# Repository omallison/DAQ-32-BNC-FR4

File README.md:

# Quartz Breakout (DAQ-32-BNC-FR4 Version)

Made in KiCad 9.0.7

- PCB is the panel (thickness: 3.2mm)
- Local (meant for short ribbon cable: [3M 8237-6000](https://www.digikey.com/en/products/detail/3m/8237-6000/26682209) connectors)
  - D connectors come out the front
  - Would be rack mounted directly above the Quartz chassis 
  - No shield grounding (differential pairs)
- D connectors lined up with the Quartz Chassis

## Panel / PCB Screen Capture 

## Quartz Chassis Comparison

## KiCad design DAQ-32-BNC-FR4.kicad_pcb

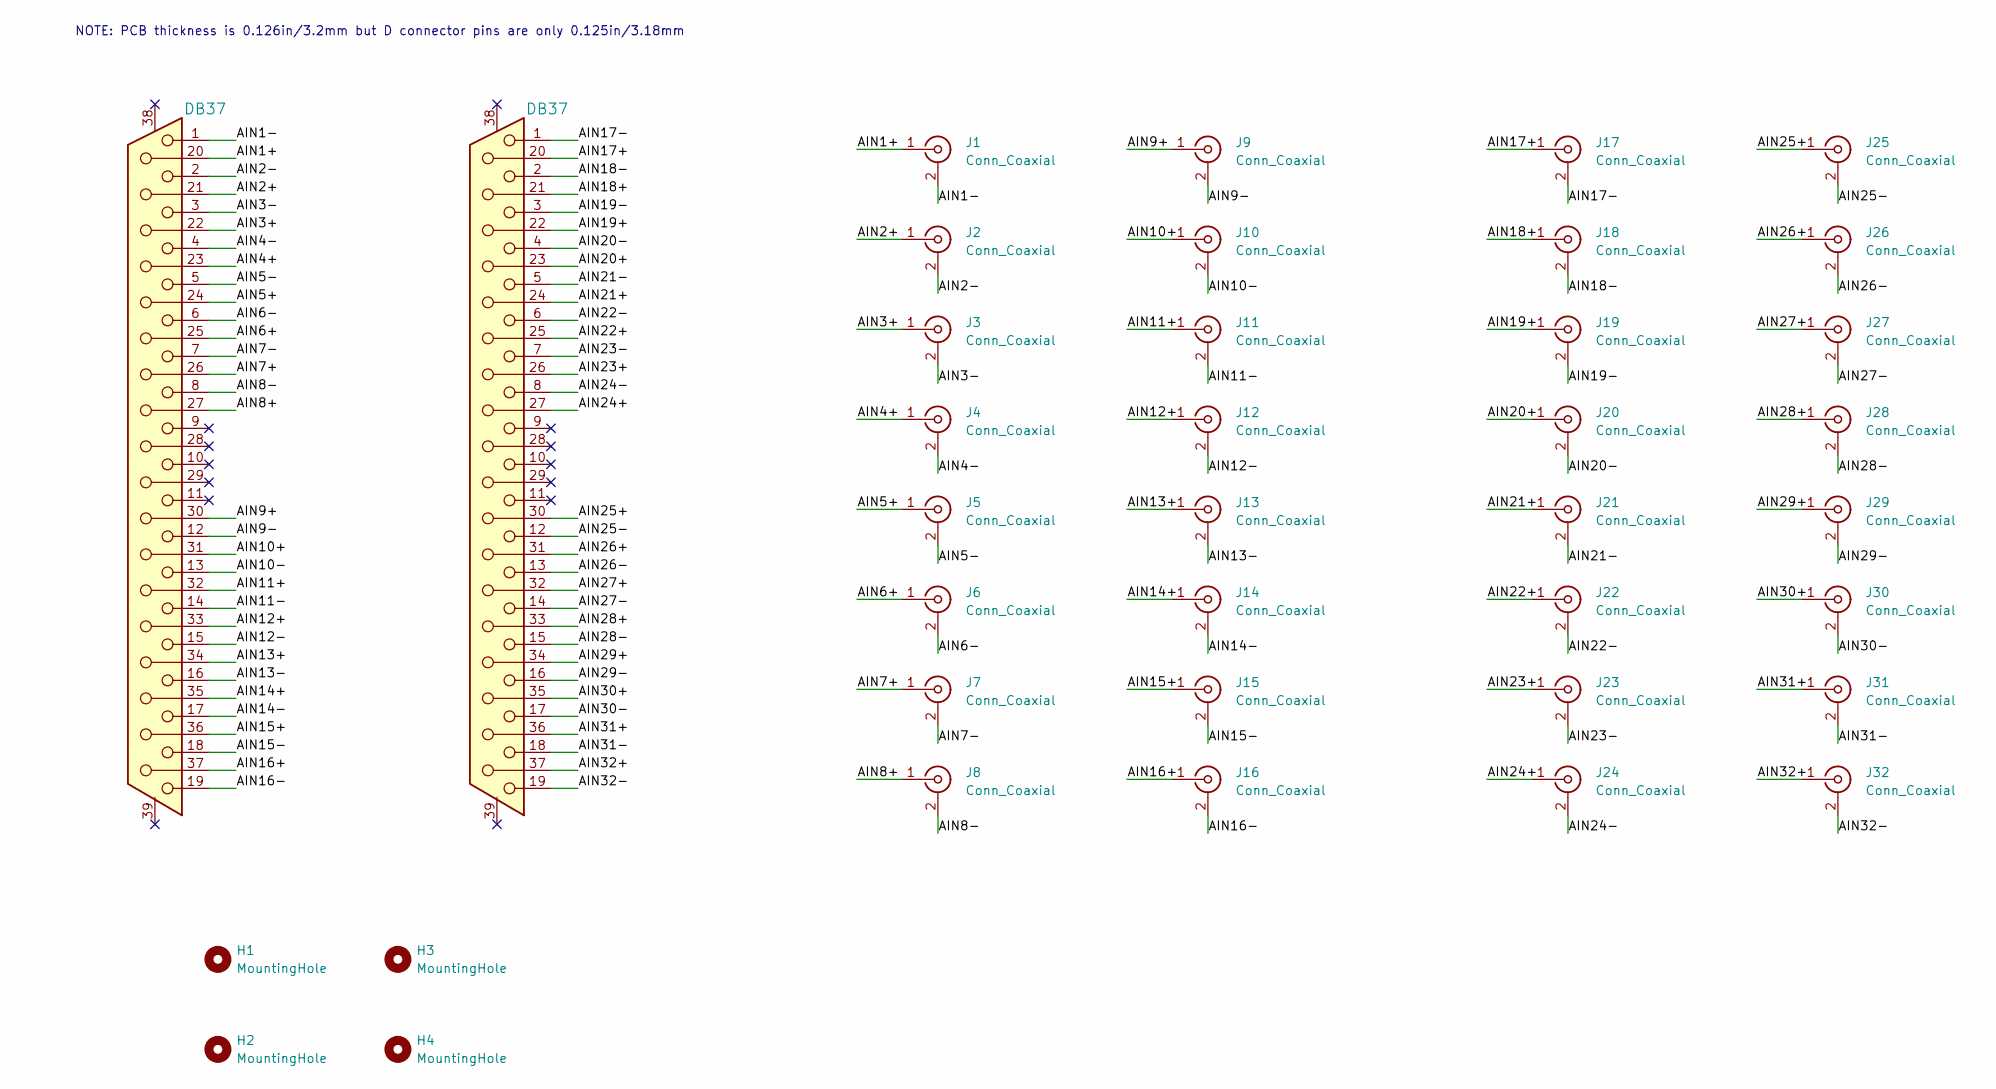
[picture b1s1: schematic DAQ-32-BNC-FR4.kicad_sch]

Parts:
H1, H2, H3, H4: MountingHole; MountingHole_19inPanel
J1, J2, J3, J4, J5, J6, J7, J8, J9, J10, J11, J12, J13, J14, J15, J16, J17, J18, J19, J20, J21, J22, J23, J24, J25, J26, J27, J28, J29, J30, J31, J32: Conn_Coaxial; CONN1_031-5329-51RFX_AMP; MPN 031-5329-51RFX
J33, J34: DB37; CONN_5787685-1_TEC; MPN 5787685-1

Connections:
/AIN1+: J1.1 (In), J33.20
/AIN1-: J1.2 (Ext), J33.1
/AIN2+: J2.1 (In), J33.21
/AIN2-: J2.2 (Ext), J33.2
/AIN3+: J3.1 (In), J33.22
/AIN3-: J3.2 (Ext), J33.3
/AIN4+: J4.1 (In), J33.23
/AIN4-: J4.2 (Ext), J33.4
/AIN5+: J5.1 (In), J33.24
/AIN5-: J5.2 (Ext), J33.5
/AIN6+: J6.1 (In), J33.25
/AIN6-: J6.2 (Ext), J33.6
/AIN7+: J7.1 (In), J33.26
/AIN7-: J7.2 (Ext), J33.7
/AIN8+: J8.1 (In), J33.27
/AIN8-: J8.2 (Ext), J33.8
/AIN9+: J9.1 (In), J33.30
/AIN9-: J9.2 (Ext), J33.12
/AIN10+: J10.1 (In), J33.31
/AIN10-: J10.2 (Ext), J33.13
/AIN11+: J11.1 (In), J33.32
/AIN11-: J11.2 (Ext), J33.14
/AIN12+: J12.1 (In), J33.33
/AIN12-: J12.2 (Ext), J33.15
/AIN13+: J13.1 (In), J33.34
/AIN13-: J13.2 (Ext), J33.16
/AIN14+: J14.1 (In), J33.35
/AIN14-: J14.2 (Ext), J33.17
/AIN15+: J15.1 (In), J33.36
/AIN15-: J15.2 (Ext), J33.18
/AIN16+: J16.1 (In), J33.37
/AIN16-: J16.2 (Ext), J33.19
/AIN17+: J17.1 (In), J34.20
/AIN17-: J17.2 (Ext), J34.1
/AIN18+: J18.1 (In), J34.21
/AIN18-: J18.2 (Ext), J34.2
/AIN19+: J19.1 (In), J34.22
/AIN19-: J19.2 (Ext), J34.3
/AIN20+: J20.1 (In), J34.23
/AIN20-: J20.2 (Ext), J34.4
/AIN21+: J21.1 (In), J34.24
/AIN21-: J21.2 (Ext), J34.5
/AIN22+: J22.1 (In), J34.25
/AIN22-: J22.2 (Ext), J34.6
/AIN23+: J23.1 (In), J34.26
/AIN23-: J23.2 (Ext), J34.7
/AIN24+: J24.1 (In), J34.27
/AIN24-: J24.2 (Ext), J34.8
/AIN25+: J25.1 (In), J34.30
/AIN25-: J25.2 (Ext), J34.12
/AIN26+: J26.1 (In), J34.31
/AIN26-: J26.2 (Ext), J34.13
/AIN27+: J27.1 (In), J34.32
/AIN27-: J27.2 (Ext), J34.14
/AIN28+: J28.1 (In), J34.33
/AIN28-: J28.2 (Ext), J34.15
/AIN29+: J29.1 (In), J34.34
/AIN29-: J29.2 (Ext), J34.16
/AIN30+: J30.1 (In), J34.35
/AIN30-: J30.2 (Ext), J34.17
/AIN31+: J31.1 (In), J34.36
/AIN31-: J31.2 (Ext), J34.18
/AIN32+: J32.1 (In), J34.37
/AIN32-: J32.2 (Ext), J34.19

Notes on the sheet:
NOTE: PCB thickness is 0.126in/3.2mm but D connector pins are only 0.125in/3.18mm

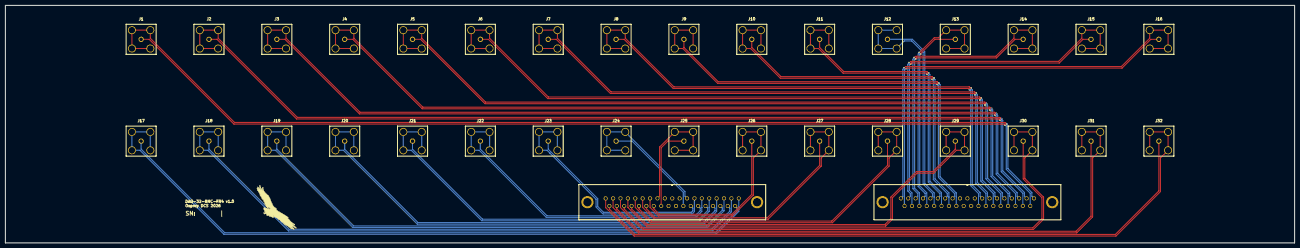
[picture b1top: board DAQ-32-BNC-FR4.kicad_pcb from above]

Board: 2 copper layers, 482.6 x 88.9 mm, 39 parts (0 on the bottom side), 64 nets.

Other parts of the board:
Logo1: Logo_Open_Hardware_Small; Logo_2X
